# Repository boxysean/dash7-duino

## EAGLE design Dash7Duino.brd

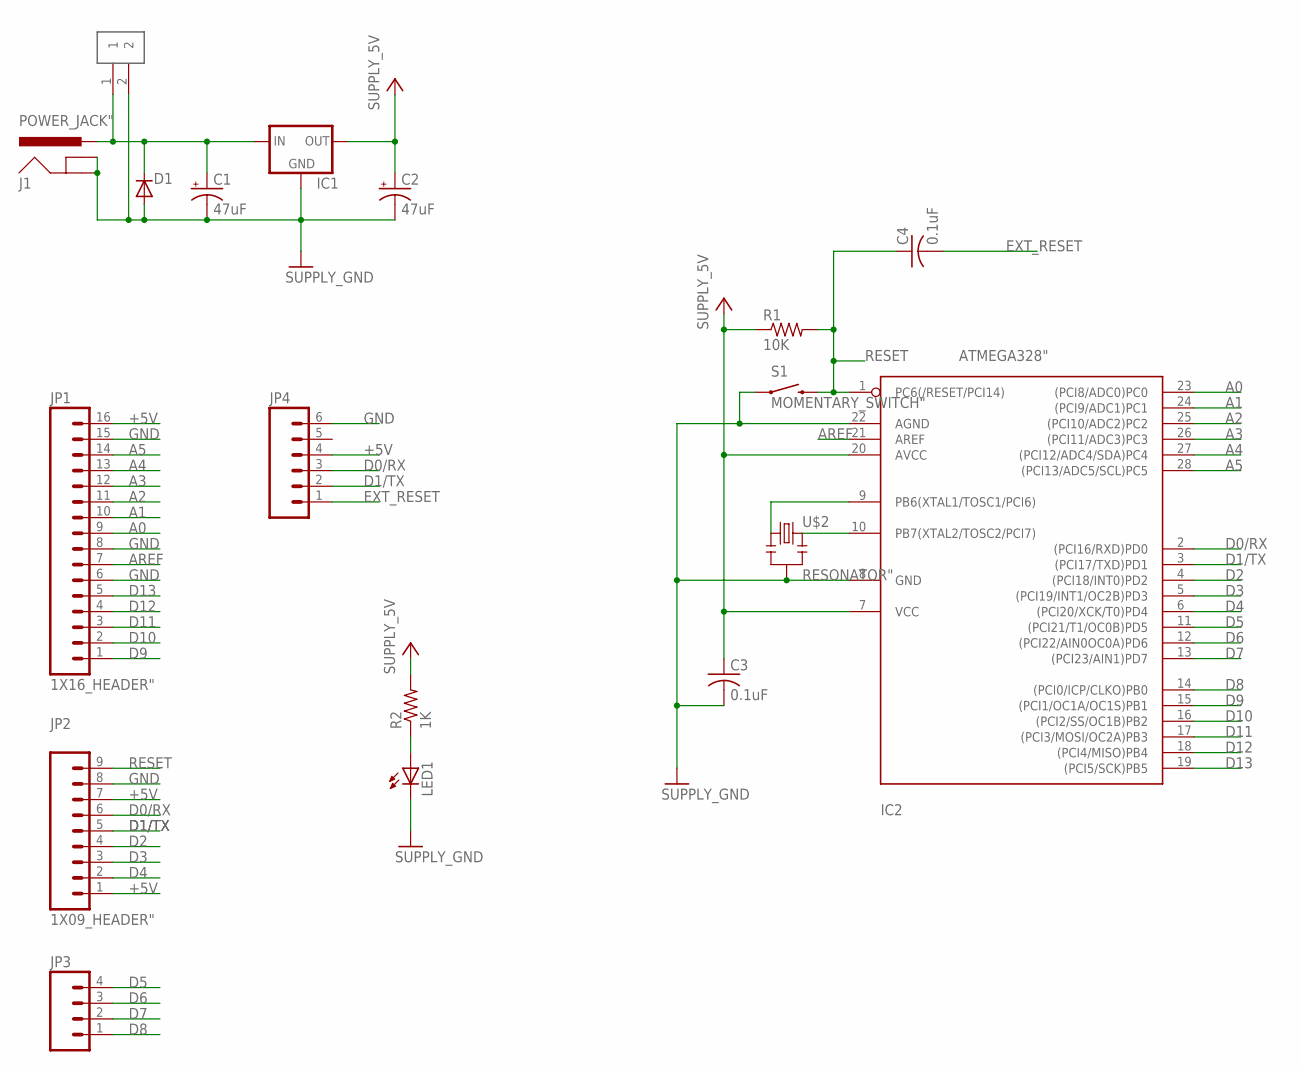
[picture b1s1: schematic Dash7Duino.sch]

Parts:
C1, C2: 47uF; ELECTROLYTIC_CAP
C3, C4: 0.1uF; UNPOLARIZED_CAP
D1: DIODE; DIODE-1N4001-KIT
IC1: REGULATOR; L4931_REGULATOR
IC2: ATMEGA328"; ATMEGA328
J1: POWER_JACK"; POWER_JACK
JP1: 1X16_HEADER"; 1X16_HEADER
JP2: 1X09_HEADER"; 1X09_HEADER
JP3: 1X04_HEADER"; 1X04_HEADER
JP4: 1X06_HEADER"; 1X06_HEADER
LED1: LED3MM; LED
R1: 10K; RESISTOR
R2: 1K; RESISTOR
S1: MOMENTARY_SWITCH"; MOMENTARY_SWITCH
U$1: 1X02_HEADER
U$2: RESONATOR"; RESONATOR

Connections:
5V: C1.+, D1.C, IC1.IN, J1.PWR, U$1.1
+5V: C2.+, C3.1, IC1.OUT, IC2.7 (VCC), IC2.20 (AVCC), JP1.16, JP2.1, JP2.7, JP4.4, R1.1, R2.2
A0: IC2.23 ((PCI8/ADC0)PC0), JP1.9
A1: IC2.24 ((PCI9/ADC1)PC1), JP1.10
A2: IC2.25 ((PCI10/ADC2)PC2), JP1.11
A3: IC2.26 ((PCI11/ADC3)PC3), JP1.12
A4: IC2.27 ((PCI12/ADC4/SDA)PC4), JP1.13
A5: IC2.28 ((PCI13/ADC5/SCL)PC5), JP1.14
AREF: IC2.21 (AREF), JP1.7
D0/RX: IC2.2 ((PCI16/RXD)PD0), JP2.6, JP4.3
D1/TX: IC2.3 ((PCI17/TXD)PD1), JP2.5, JP4.2
D2: IC2.4 ((PCI18/INT0)PD2), JP2.4
D3: IC2.5 ((PCI19/INT1/OC2B)PD3), JP2.3
D4: IC2.6 ((PCI20/XCK/T0)PD4), JP2.2
D5: IC2.11 ((PCI21/T1/OC0B)PD5), JP3.4
D6: IC2.12 ((PCI22/AIN0OC0A)PD6), JP3.3
D7: IC2.13 ((PCI23/AIN1)PD7), JP3.2
D8: IC2.14 ((PCI0/ICP/CLKO)PB0), JP3.1
D9: IC2.15 ((PCI1/OC1A/OC1S)PB1), JP1.1
D10: IC2.16 ((PCI2/SS/OC1B)PB2), JP1.2
D11: IC2.17 ((PCI3/MOSI/OC2A)PB3), JP1.3
D12: IC2.18 ((PCI4/MISO)PB4), JP1.4
D13: IC2.19 ((PCI5/SCK)PB5), JP1.5
EXT_RESET: C4.2, JP4.1
GND: C1.-, C2.-, C3.2, D1.A, IC1.GND, IC2.8 (GND), IC2.22 (AGND), J1.GND, J1.GNDBREAK, JP1.6, JP1.8, JP1.15, JP2.8, JP4.6, LED1.K (C), S1.1, U$1.2, U$2.2
unnamed: IC2.9 (PB6(XTAL1/TOSC1/PCI6)), U$2.1
unnamed: IC2.10 (PB7(XTAL2/TOSC2/PCI7)), U$2.3
unnamed: LED1.A, R2.1
RESET: C4.1, IC2.1 (PC6(/RESET/PCI14)), JP2.9, R1.2, S1.3 (2)

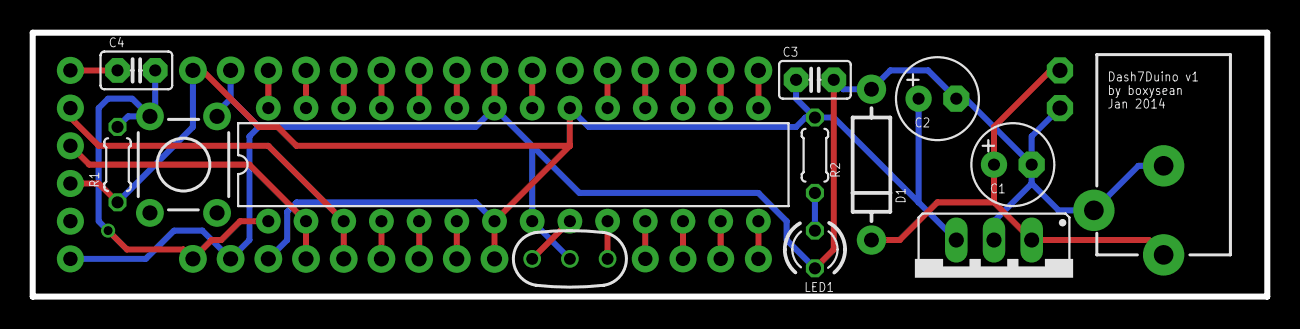
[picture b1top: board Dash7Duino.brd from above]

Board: 2 copper layers, 83.2 x 17.8 mm, 18 parts (0 on the bottom side), 29 nets.

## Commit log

2014-01-22 almost done
2014-01-22 rev1 completed...

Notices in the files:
parts and their libraries:
SparkFun-DiscreteSemi: Licensing: CC v3.0 Share-Alike You are welcome to use this library for commercial purposes.
